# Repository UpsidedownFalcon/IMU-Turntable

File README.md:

# High-Tech Fidget Spinner V2: "Treexelator-PRO-T2000"

Welcome! 

This is an open-source project for the construction of a 3-DoF IMU turntable, its the second version of the "High-Tech Fidget Spinner". our main goal is to increase the sensitivity of the testing device and make it more accurate while keeping the cost down as low as possible. 
Our goal is to have 0.001 degree of sensitivity. 
This is a ongoing project and will be updated...

Approximate Timeline

Captain's Journal:

18/10/2025: Did a prelimery research about which components to use, tought about using REV robotics sparc flex + neo vortex combo due to their lib support and internal decoder inside the esc, decided to use CAN bus to communicate.

22/10/2025: Did more research and understood the spark flex and neo are not a good choise for this device, their quality is mehhh, and the max bit support of spark flec is around 200000 increments per sec which is nothing with high sensitivity encoder and some speed, decided to look at other compoennts and my research directed me towards Odrive Pro ESC

23/10/2025: Designed a basic mass model for the device and calculated the torque needed to accelerate it at all axeses from 0 rpm to 60 rpm in 1 second, the report can be found at github site, then did a research for motors and found cubemars gl series, they are desiged for gimbal use with butter smooth operation, altough pricey, they were a really good match.

2/11/2025: Did some research for the microcontrollers, the Odrive Pros have stm32H7s as their microcontroller, after some research about STM32H7 microchip, I realized it was much better than any esp32 ı could use and decided to use STM32H723, it support ethernet, I3C, I2C, Uart, SPI, Usart, CAN, SAI, QSPI etc, as this is a machine to test different sensors, this microcontroller can comminicate with anything ı threw at.

3/11/2025: Opened this branch after getting approved by the owner.

5/11/2025: Ordered (Most) the part that are in the BoM (Bill of Materials), please find atteched the BoM, the datasheets, model numbers, URL to buy, descriptions can be found.

6/11/2025: Ordered more parts.

8/11/2025-12/11/2025: Some part have arrived still waiting for the slip rings, aksim encoders, and need to order bearings.

10/11/2025: Started designing the 3rd axis.

14/11/2025: read few document about acl testing for the injury sim jig, had more idea about what to do.

15/11/2025: Finished Designing the 3rd axis and submittedi it.

20/11/2025: Started doing research on the tolorances we have for the mechanical parts and different manufacturning methods.

23/11/2025: did more research about tolorances usign GD&T, started writing the report for manufacturing.

22/11/2025: contacted DHL and RLS for products and shipment, made few calls with DHL, solved a problem with their system, RLS changed prices, asked them to understand if we can get our price diff back, (Note: no reply:( 

26/11/2025: submitted the GD&T report to higher ups. 

27/11/2025: started to do the manufacturing report about the types of manufacturing we can use and their prices.

01/12/2025: finished doing the materials/manufacturing report, can be accessed in github.

5/12/2025: started doing the 2nd and 3rd axes, the design is being done using fusion 360. 

8/12/2025: finished the V1 of the desing, all ground plate, 1st axis, 2nd axis, 3rd axis, and the sensor plate is ready for 3d prinitng for prototyping. 3d printing is only for model and does not have the tolorances we need. 

10/12/2025: did some fine adjustment to the 3d design.

12/12/2025: sliced the components: ground body and axis 1 to two pieces to be able to print them using bambulab x1c

15/12/2025: sent the 3d body files for printing.

19/12/2025: did the first prototype. find the photo in the repository.

20/12/2025: updated the design, fixed some faulty diameters, optimized encoder to ring distance, printed the ground body.

21/12/2025: printed the new optimized design and put them together. made edits to the design for slip ring adjustment. 

22/12/2025: finished the new prototype. its ready to be sent to a cnc manufacturer.

24/12/2025: edited the design again and produced 2d dxf files for GD&T, got a quote from jlc

24/12/2025-03/01/2026: had tens of emails with jlc cnc team and change the design more then 10 times because quote "it was too complex" in the words of jlc team. in the end after multiple iterations we got a quote of 3237.3 usd plus tax, the original quote was 1300usd. this is ridiculous. i have contacted jlc cnc team again and they just told me to change the design again which is frustrating. its awful to work with them. for the future person who is reading this: DO NOT WORK WİTH JLC CNC EVER. 

Future Goals: finish modelling/prototyping by 20th of december, and then order the parts from JLC CNC from 7075 alum with 50 micron tolorance.
Finish the products as soon as the CNC parts arrive,
Write firmware for the treexelator for it to give the data we want in the format we want also being easy to read (GUI)
the timetable can be seen in the "timetable" image above.

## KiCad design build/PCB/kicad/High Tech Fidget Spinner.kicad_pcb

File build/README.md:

# ```/build/``` 

This directory contains files and instructions to build the mechanical and electronic parts of the High-Tech Fidget Spinner. 

```
├── CAD/                       # Contains all of the required CAD files 
├── PCB/                       # Contains all of the required PCB files 
├── assembly-guide.md          # Assembly guide
├── BoM.md                     # Bill of materials 
└── README.md
```

## ```/build/CAD/``` 
- [```./3D Print Files/```](/build/CAD/3D%20Print%20Files/) contains **.3mf** files for 3D-printing 
- Contains *.3mf*, *.f3z*, *.step* and *.stl* **assembly** files for the project
    - These can be opened in your preferred CAD software for modification 

## ```/build/PCB/``` 
- [```./GERBER/```](/build/PCB/GERBER/) contains GERBER files for PCB manufacture 
    - [```./GERBER/Drill Files```](/build/PCB/GERBER/Drill%20Files/) contains drill files for PCB manufacture 
- [```./kicad/```](/build/PCB/kicad/) contains KiCad project files <--- OPEN THE PROJECT FILE WITH **KICAD 9.0** 
- [```./schematic.pdf```](/build/PCB/schmeatic.pdf) contains the schematic for the electronics 

## ```/build/assembly-guide.md```
This document explains how to complete the 

- mechanical assembly 
- electronic assembly 

for the High-Tech fidget spinner. 

## ```/build/BoM.md``` 
This document is the bill of materials for High-Tech Fidget Spinner. 

## Start building! 

0) Familiarise yourself with [```/build/assembly-guide.md```](/build/assembly-guide.md) 
1) Source the components from [```/build/BoM.md```](/build/BoM.md) 
2) Follow the instructions in [```/build/assembly-guide.md```](/build/assembly-guide.md) 
3) Test and tweak!

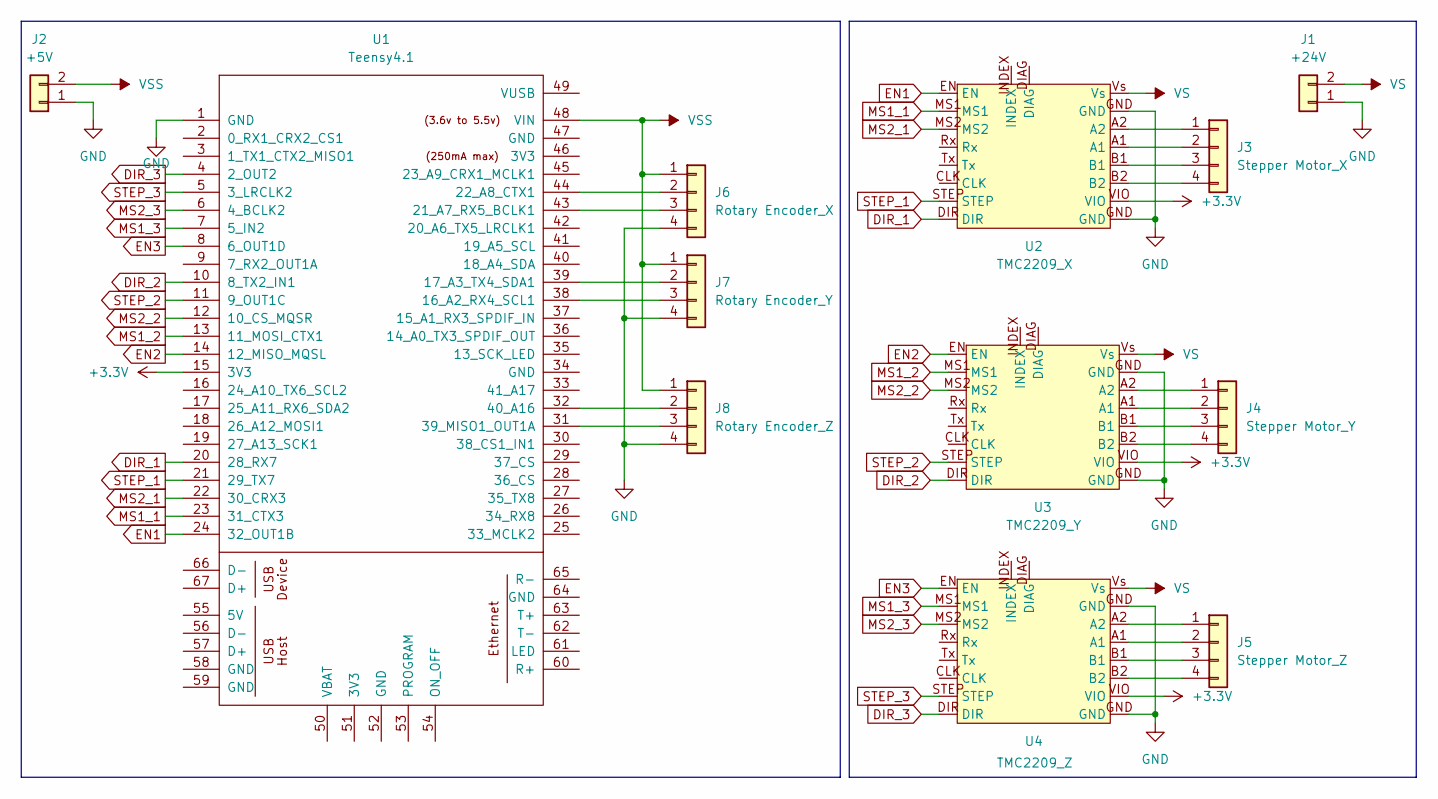
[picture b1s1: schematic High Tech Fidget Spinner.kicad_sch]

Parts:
J1: +24V; PinHeader_1x02_P2.54mm_Vertical
J2: +5V; PinHeader_1x02_P2.54mm_Vertical
J3: Stepper Motor_X; PinHeader_1x04_P2.54mm_Vertical
J4: Stepper Motor_Y; PinHeader_1x04_P2.54mm_Vertical
J5: Stepper Motor_Z; PinHeader_1x04_P2.54mm_Vertical
J6: Rotary Encoder_X; PinHeader_1x04_P2.54mm_Vertical
J7: Rotary Encoder_Y; PinHeader_1x04_P2.54mm_Vertical
J8: Rotary Encoder_Z; PinHeader_1x04_P2.54mm_Vertical
U1: Teensy4.1; Teensy41
U2: TMC2209_X; TMC2209
U3: TMC2209_Y; TMC2209
U4: TMC2209_Z; TMC2209

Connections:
+3.3V: U1.15 (3V3), U2.VIO, U3.VIO, U4.VIO
DIR_1: U1.20 (28_RX7), U2.DIR
DIR_2: U1.10 (8_TX2_IN1), U3.DIR
DIR_3: U1.4 (2_OUT2), U4.DIR
EN1: U1.24 (32_OUT1B), U2.EN
EN2: U1.14 (12_MISO_MQSL), U3.EN
EN3: U1.8 (6_OUT1D), U4.EN
GND: J1.1, J2.1, J6.4, J7.4, J8.4, U1.1 (GND), U2.GND, U3.GND, U4.GND
MS1_1: U1.23 (31_CTX3), U2.MS1
MS1_2: U1.13 (11_MOSI_CTX1), U3.MS1
MS1_3: U1.7 (5_IN2), U4.MS1
MS2_1: U1.22 (30_CRX3), U2.MS2
MS2_2: U1.12 (10_CS_MQSR), U3.MS2
MS2_3: U1.6 (4_BCLK2), U4.MS2
unnamed: J3.1, U2.A2
unnamed: J3.2, U2.A1
unnamed: J3.3, U2.B1
unnamed: J3.4, U2.B2
unnamed: J4.1, U3.A2
unnamed: J4.2, U3.A1
unnamed: J4.3, U3.B1
unnamed: J4.4, U3.B2
unnamed: J5.1, U4.A2
unnamed: J5.2, U4.A1
unnamed: J5.3, U4.B1
unnamed: J5.4, U4.B2
unnamed: J6.2, U1.44 (22_A8_CTX1)
unnamed: J6.3, U1.43 (21_A7_RX5_BCLK1)
unnamed: J7.2, U1.39 (17_A3_TX4_SDA1)
unnamed: J7.3, U1.38 (16_A2_RX4_SCL1)
unnamed: J8.2, U1.32 (40_A16)
unnamed: J8.3, U1.31 (39_MISO1_OUT1A)
STEP_1: U1.21 (29_TX7), U2.STEP
STEP_2: U1.11 (9_OUT1C), U3.STEP
STEP_3: U1.5 (3_LRCLK2), U4.STEP
VS: J1.2, U2.Vs, U3.Vs, U4.Vs
VSS: J2.2, J6.1, J7.1, J8.1, U1.48 (VIN)

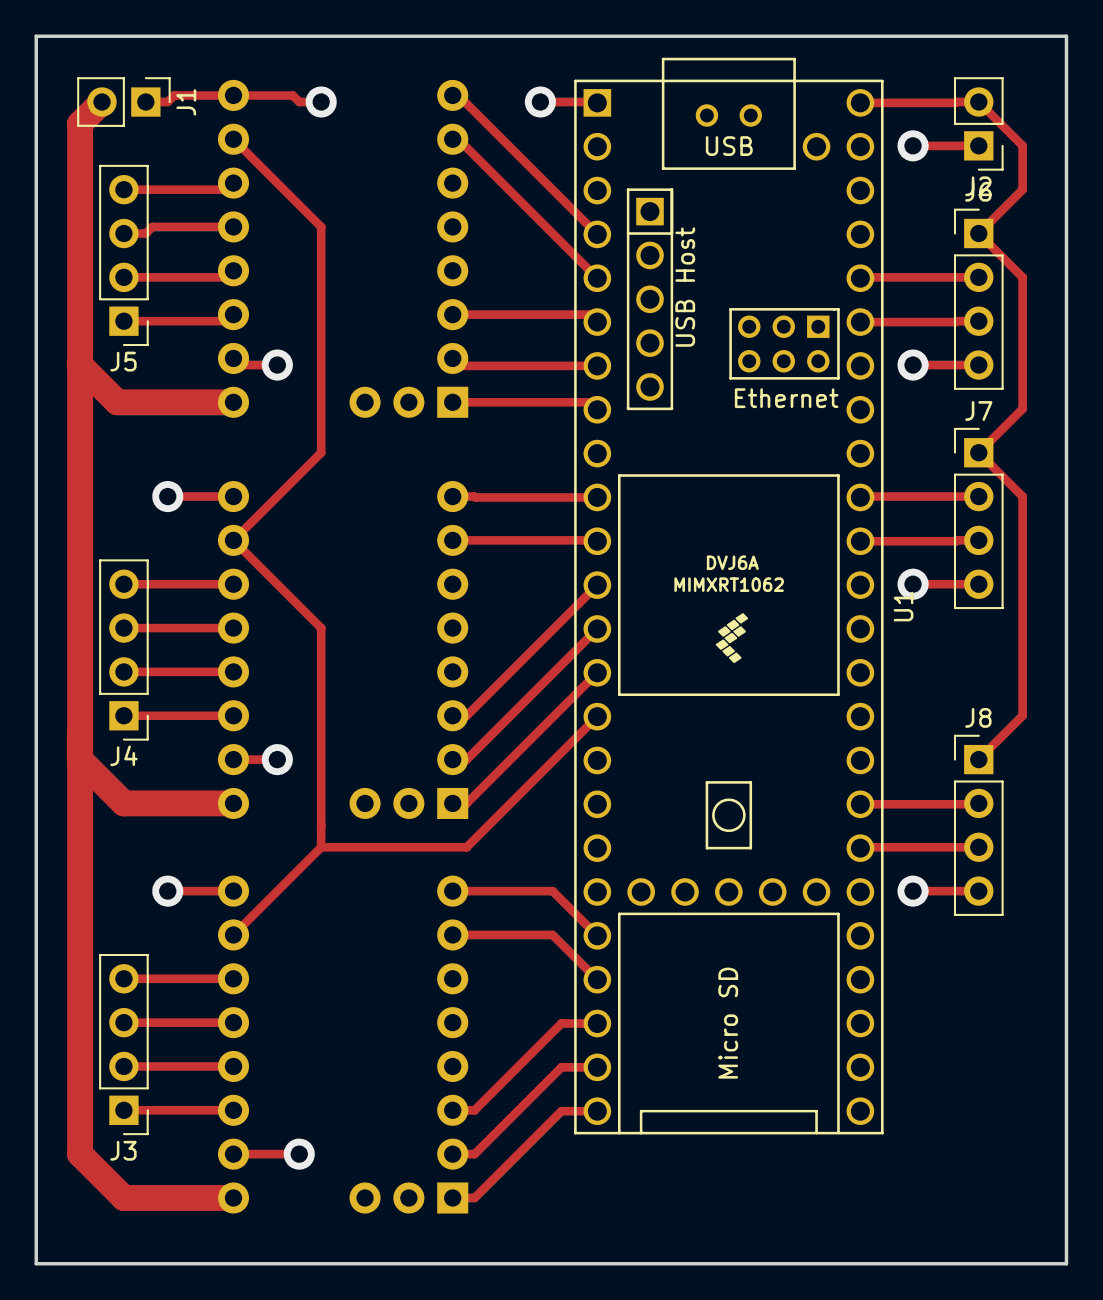
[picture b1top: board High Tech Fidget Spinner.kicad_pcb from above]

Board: 2 copper layers, 59.7 x 71.1 mm, 12 parts (0 on the bottom side), 37 nets.

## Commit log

2025-05-27 Converted .txt to .md
2025-05-27 Added research proposal
2025-05-27 fixed README.md
2025-05-27 Created PRD
2025-05-27 Updated PRD
2025-05-27 Wrote "Document" with CUM
2025-06-03 stepper iteration
2025-06-03 stepper initial ideas
2025-06-04 Updataed PRD
2025-06-05 Stepper data
2025-06-27 1 stepper working
2025-06-28 webapp
2025-06-30 trajectory planning
2025-06-30 trajectory transfer
2025-06-30 trajectory written to SD
2025-07-17 Paper submission
2025-08-01 structured-github
2025-08-01 GNU GPLv3 licence
2025-08-01 GNU GPLv3 licence added
2025-08-04 Added READMEs to all directories
2025-08-04 Update READMEs
2025-08-04 Updat assembly-guide
2025-08-04 added tpu mount
2025-08-04 Added BoM
2025-08-04 wrote usage guide
2025-08-04 final conference paper
2025-08-04 Thumbnail + .bbl
2025-09-23 Corrected conference paper with balanced references page
2025-09-27 Kicad update
2025-09-27 PlatformIO
2025-09-27 SD Card Test
2025-09-28 Slip ring PCBs
2025-09-28 3 axist test
2025-10-01 slip rings
2025-10-01 New PIO Project for Deployable FW
2025-10-06 New PIO BE
2025-10-06 FreeRTOS FW in PIO
2025-11-02 Delete build/CAD/3D Print Files directory
    deleted from the branch to avoid confusion
2025-11-02 Delete build directory
    deleted from the branch to avoid confusion
2025-11-02 Delete docs directory
    deleted from the branch to avoid confusion
2025-11-02 Delete src directory
    deleted from the branch to avoid confusion
2025-11-02 Delete testing directory
    deleted from the branch to avoid confusion
2025-11-02 Delete tools directory
    deleted from the branch to avoid confusion
2025-11-02 Update README.md
    updated for the second model
2025-11-02 Update README.md
    updated
2025-11-19 FW update
2025-12-03 Add files via upload
    manufacturing related update
2025-12-10 Add files via upload
    First whole prototype
2025-12-15 Rename Treexalerator.f3d to Treexalerator assembly V6.f3d
2025-12-19 fixed typo
2026-01-04 Create Assembly
